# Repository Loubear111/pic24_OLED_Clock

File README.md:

# pic24_OLED_Clock
A RTC and OLED project for the PIC24FJ64GA002 Microcontroller. This project uses the Adafruit 1.3" Monochrome OLED display as well as the RTC module on the PIC to create an interactive clock and stopwatch with alarm functions.

**PIC24 Microcontroller** - https://www.microchip.com/wwwproducts/en/PIC24FJ64GA002 \
**Adafruit Display** - https://www.adafruit.com/product/938 \
**chipKIT Programmer** - https://store.digilentinc.com/chipkit-pgm-programmer-debugger-for-use-with-digilent-chipkit-platforms/

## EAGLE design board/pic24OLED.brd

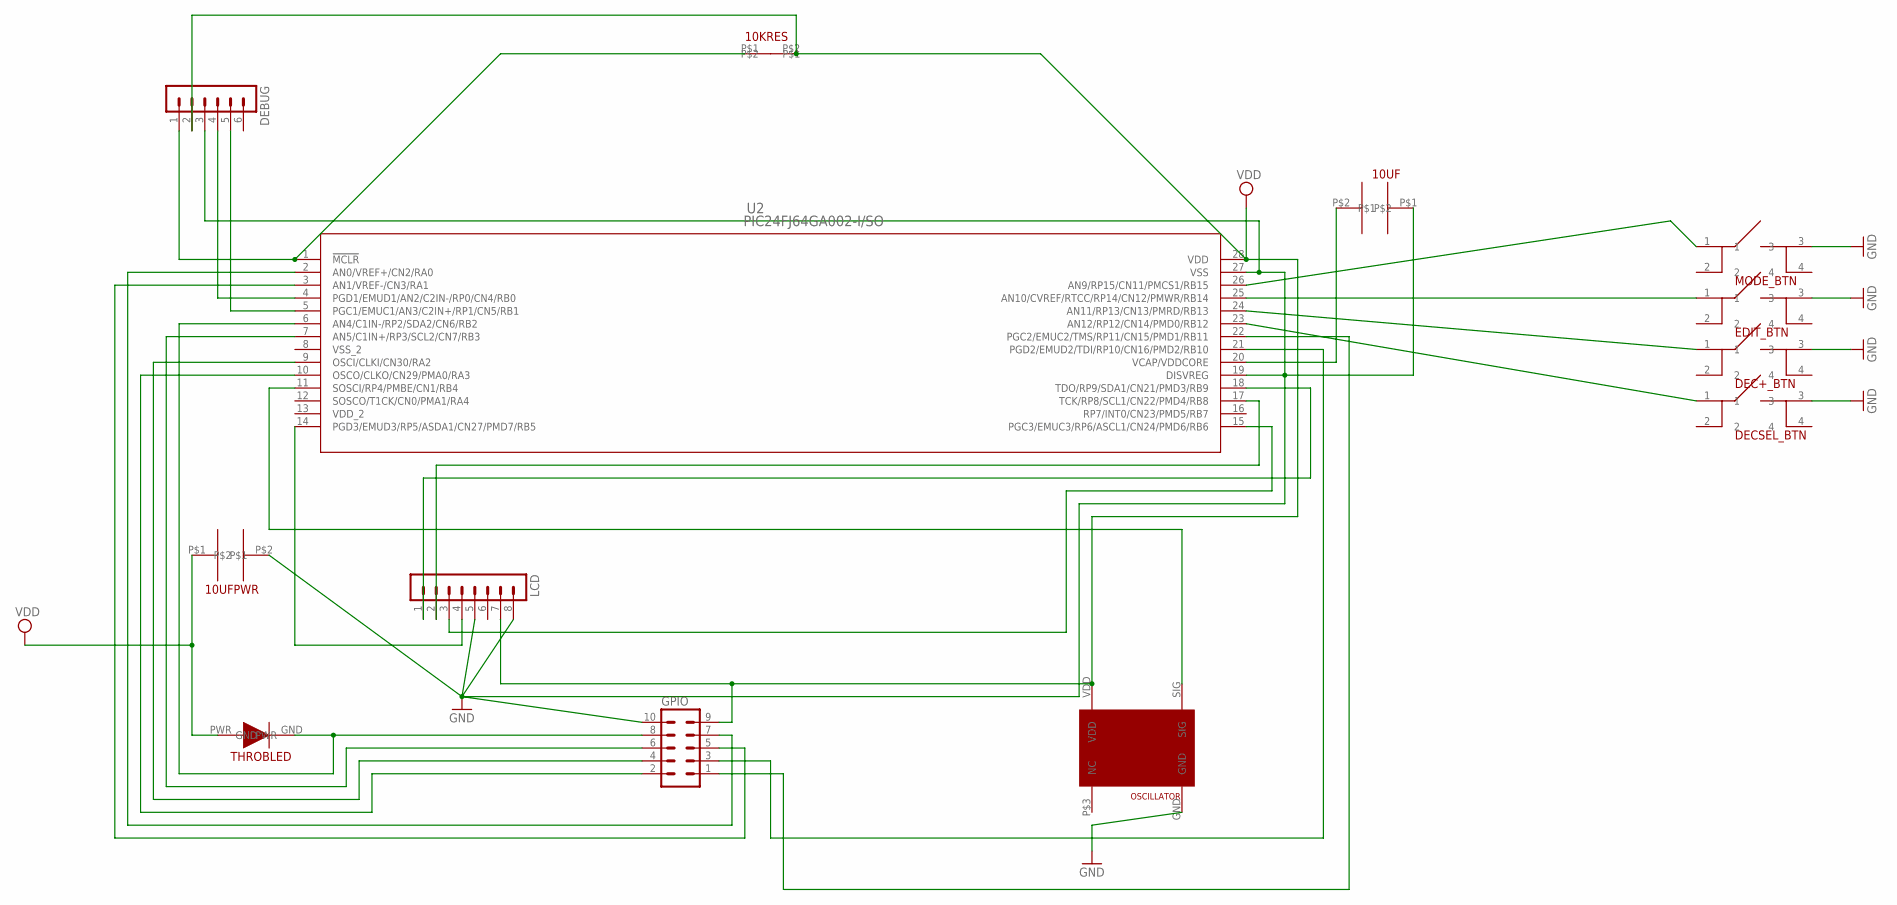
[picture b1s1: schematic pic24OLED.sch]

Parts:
10KRES: THRESISTOR
10UF, 10UFPWR: THCAP
DEBUG: MA06-1
DEC+_BTN: PTS645-BUTTONPTS645; TL3315-BUTTON
DECSEL_BTN: PTS645-BUTTONPTS645; TL3315-BUTTON
EDIT_BTN: PTS645-BUTTONPTS645; TL3315-BUTTON
GPIO: MA05-2
LCD: MA08-1
MODE_BTN: PTS645-BUTTONPTS645; TL3315-BUTTON
OSCILLATOR: LX0-32.768OSCILLATOR
THROBLED: THLED
U2: PIC24FJ64GA002-I/SO; SOIC28-W_MC

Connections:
GND: 10UF.P$1, 10UFPWR.P$2, DEBUG.3, DEC+_BTN.3, DECSEL_BTN.3, EDIT_BTN.3, GPIO.10, LCD.5, LCD.8, MODE_BTN.3, OSCILLATOR.GND, U2.19 (DISVREG), U2.27 (VSS)
unnamed: 10KRES.P$1, DEBUG.1, U2.1 (!MCLR)
unnamed: GPIO.4, U2.9 (OSCI/CLKI/CN30/RA2)
unnamed: MODE_BTN.1, U2.26 (AN9/RP15/CN11/PMCS1/RB15)
unnamed: EDIT_BTN.1, U2.25 (AN10/CVREF/RTCC/RP14/CN12/PMWR/RB14)
unnamed: DEC+_BTN.1, U2.24 (AN11/RP13/CN13/PMRD/RB13)
unnamed: DECSEL_BTN.1, U2.23 (AN12/RP12/CN14/PMD0/RB12)
unnamed: LCD.4, U2.14 (PGD3/EMUD3/RP5/ASDA1/CN27/PMD7/RB5)
unnamed: LCD.3, U2.15 (PGC3/EMUC3/RP6/ASCL1/CN24/PMD6/RB6)
unnamed: LCD.2, U2.17 (TCK/RP8/SCL1/CN22/PMD4/RB8)
unnamed: LCD.1, U2.18 (TDO/RP9/SDA1/CN21/PMD3/RB9)
unnamed: 10UF.P$2, U2.20 (VCAP/VDDCORE)
unnamed: GPIO.6, U2.7 (AN5/C1IN+/RP3/SCL2/CN7/RB3)
unnamed: OSCILLATOR.SIG, U2.11 (SOSCI/RP4/PMBE/CN1/RB4)
unnamed: GPIO.8, THROBLED.GND, U2.6 (AN4/C1IN-/RP2/SDA2/CN6/RB2)
unnamed: DEBUG.4, U2.4 (PGD1/EMUD1/AN2/C2IN-/RP0/CN4/RB0)
unnamed: DEBUG.5, U2.5 (PGC1/EMUC1/AN3/C2IN+/RP1/CN5/RB1)
unnamed: GPIO.2, U2.10 (OSCO/CLKO/CN29/PMA0/RA3)
unnamed: GPIO.7, U2.2 (AN0/VREF+/CN2/RA0)
unnamed: GPIO.5, U2.3 (AN1/VREF-/CN3/RA1)
unnamed: GPIO.3, U2.21 (PGD2/EMUD2/TDI/RP10/CN16/PMD2/RB10)
unnamed: GPIO.1, U2.22 (PGC2/EMUC2/TMS/RP11/CN15/PMD1/RB11)
VDD: 10KRES.P$2, 10UFPWR.P$1, DEBUG.2, GPIO.9, LCD.7, OSCILLATOR.VDD, THROBLED.PWR, U2.28 (VDD)

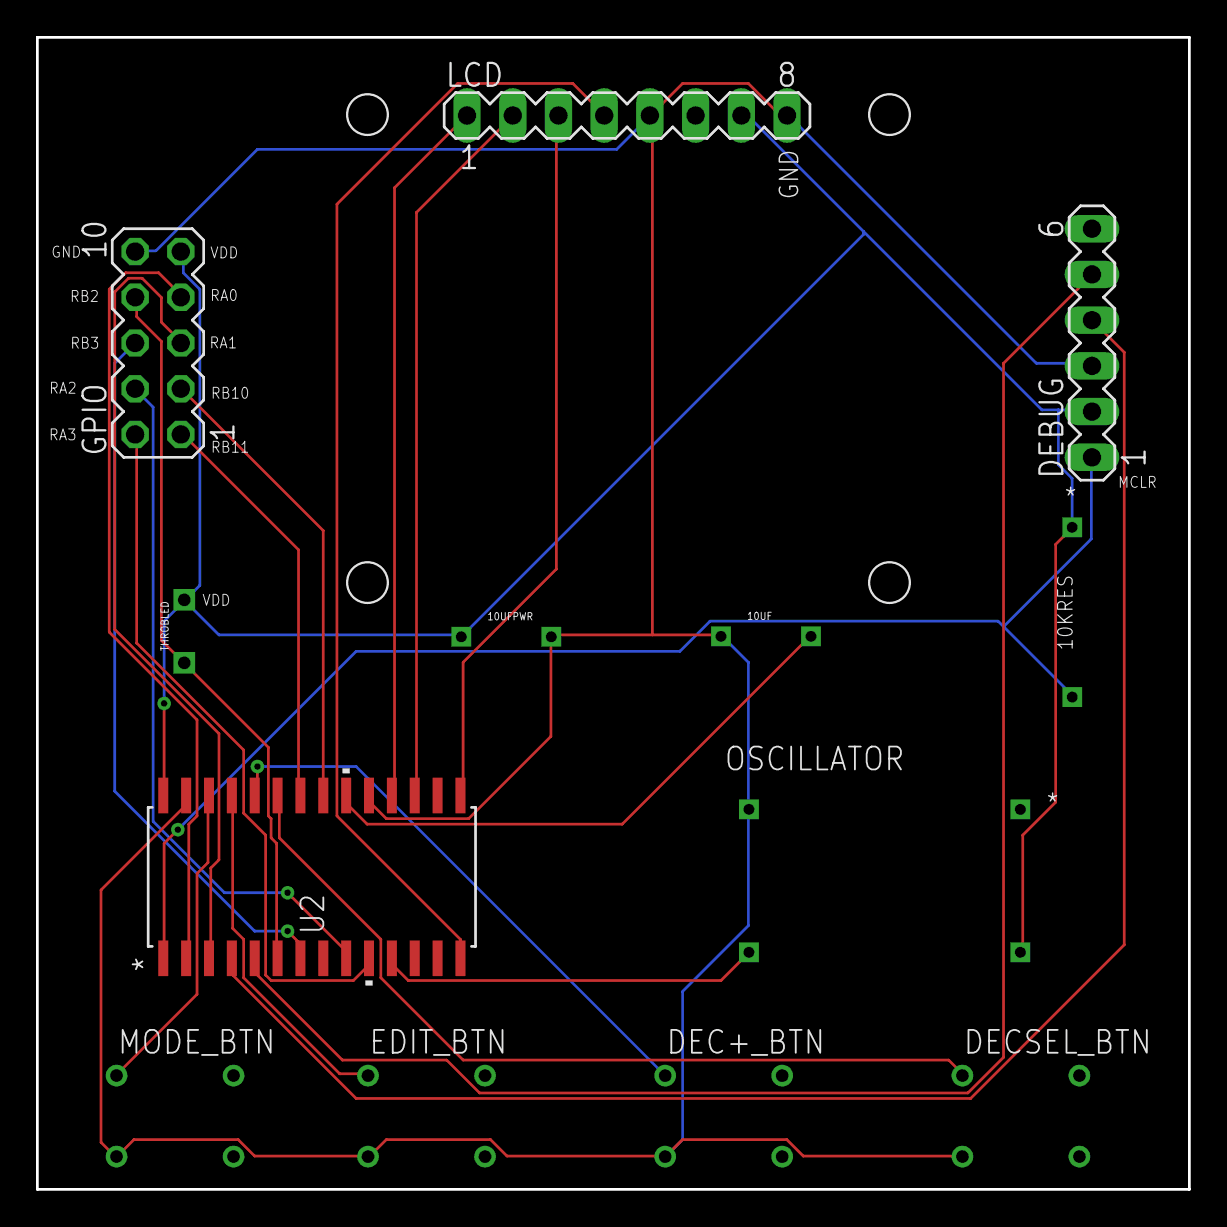
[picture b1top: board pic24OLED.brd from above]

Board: 2 copper layers, 64.0 x 64.0 mm, 13 parts (0 on the bottom side), 23 nets.

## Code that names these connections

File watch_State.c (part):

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    }
    else
    {
        //PORTBbits.RB2 = 0;
    }
    
}
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    //these ports will read high when there is not click but read low when a click occurs because they will short        
    //this is where we will set the pull up resistor
    //setting a pullup module on device pins 23-26  or RP(12-15) or RB(12-15)
    CNPU1bits.CN11PUE = 1;      //RB15
    CNPU1bits.CN12PUE = 1;      //RB14
    CNPU1bits.CN13PUE = 1;      //RB13
    CNPU1bits.CN14PUE = 1;      //RB12
    
}

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
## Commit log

2019-04-22 Initial working code. Can write bits to the display!
    First working version of the code. SPI communicates correctly with the display. Had to make sure SPI was communicating in 8 bit segments rather than the default 16 bit segments.
2019-04-23 Added functionality to write a '1'
    can now write a 1 to the screen. This was to test if the program that translates a bitmap to an array will work for us. It does, but weirdly only if the width of the character is 8 bits (or maybe a m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
2019-04-25 Ported LCD functions to a standalone library
    We can now write strings to the LCD at given x and y values. Currently can only write numbers 1-9.
2019-04-29 RTC WIP
2019-05-01 Fully functioning RTC
    RTC is now fully implemented with our handy external 32.768 kHz clock from Ax-Man. Now all we need to do is implement the currently skeleton-of-a-state-machine into a fully functioning state machine.
2019-05-03 Got setting of time setup correctly
2019-05-04 Alarm now implemented
2019-05-05 Final commit before our final presentation!
2019-05-05 Create LICENSE
2019-05-08 Fixes few small glitches with edit mode.
2019-06-27 Added first draft of board schematics to repo
2019-06-27 Finished up first board draft completely.
2019-06-27 removed unused file
2019-07-26 Board design v1.1
    Used PIC layout I can actually solder. Moved some things around for easier access and made holes bigger.
2019-07-26 Updated library file
2019-08-24 Removed blocking button delay code and replaced with non-blocking debounce delay.
    Buttons could still use work as the don't detect button releases. To correctly capture buttons and make them not feel clunky we'll need to use button presses/releases to tell when actions happen.
2019-08-24 Added assembled v1.1 board photo
2019-08-24 resized board image
2019-08-24 added README file
2019-08-26 Fixed up button state machine to handle clicks rather than just presses for better feel when user clicks. Updated .gitignore.
2019-08-26 updated README with products
